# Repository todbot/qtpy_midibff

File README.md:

# qtpy_midibff

QTPy MIDI BFF — a small MIDI interface board for QTPy / Xiao class boards (RP2040 or compatible).
The board breaks out the host MCU's hardware UART to standard MIDI IN and MIDI OUT jacks (TRS or 5-pin DIN).

## Hardware

The PCB is meant for easy assembly using only through-hole components. 
It is essentialy a QTPy "doubler" with a standard MIDI In and MIDI Out circuit, 
with a 4-pin I2C header for a standard OLED display (usually 128x32 SSD1306).

## Assembling

_Coming soon._

## Arduino sketches

Requires [arduino-pico](https://arduino-pico.readthedocs.io/en/latest/install.html) board core.

Set **Tools > USB Stack: Adafruit TinyUSB** before uploading any sketch.

Libraries needed (Arduino Library Manager):
- [Adafruit TinyUSB](https://github.com/adafruit/Adafruit_TinyUSB_Arduino)
- [MIDI Library](https://github.com/FortySevenEffects/arduino_midi_library)
- [Adafruit SSD1306](https://github.com/adafruit/Adafruit_SSD1306) + [Adafruit GFX Library](https://github.com/adafruit/Adafruit-GFX-Library) _(OLED sketches only)_
- [Adafruit SPIFlash](https://github.com/adafruit/Adafruit_SPIFlash) + [SdFat - Adafruit Fork](https://github.com/adafruit/SdFat) + [ArduinoJson](https://arduinojson.org) _(MSC sketch only)_

### `midi_interface` — USB-MIDI ↔ UART-MIDI bridge

[`arduino/midi_interface/`](arduino/midi_interface/)

Forwards all MIDI between USB and UART in both directions. Includes scaffolding to filter or
transform messages — uncomment the examples or add your own:

- Drop realtime messages (clock, active sensing, etc.)
- Transpose notes on a channel
- Remap channels

```
arduino-cli compile \
  --fqbn rp2040:rp2040:adafruit_qtpy:usbstack=tinyusb \
  arduino/midi_interface
```

SysEx messages up to 127 bytes are forwarded. See the source for notes on larger SysEx.

### `midi_interface_oled` — bridge with OLED display

[`arduino/midi_interface_oled/`](arduino/midi_interface_oled/)

Same bridge as `midi_interface`, with a 128x32 SSD1306 I2C OLED that displays each incoming
message. Realtime messages (clock, active sensing) are forwarded but not shown, to avoid flicker.

```
arduino-cli compile \
  --fqbn rp2040:rp2040:adafruit_qtpy:usbstack=tinyusb \
  arduino/midi_interface_oled
```

### `midi_interface_msc` — bridge with USB flash drive and config file

[`arduino/midi_interface_msc/`](arduino/midi_interface_msc/)

Extends `midi_interface_oled` with a USB Mass Storage device backed by the RP2040's internal
flash (the filesystem partition). The drive contains a `config.json` file that controls runtime
behaviour — no recompile needed to change settings.

```json
{
  "name": "MIDI BFF",
  "manufacturer": "todbot",
  "filter_realtime": false,
  "transpose": 0
}
```

Edit `config.json` on the drive, eject it, then reset the board to apply the new settings.
The `filter_realtime` and `transpose` fields are applied in both directions.

Requires a board Flash Size setting that includes a 1MB filesystem partition. Compile commands for each supported board:

```
# QTPy RP2040 (8MB flash)
arduino-cli compile \
  --fqbn rp2040:rp2040:adafruit_qtpy:usbstack=tinyusb,flash=8388608_1048576 \
  arduino/midi_interface_msc

# Xiao RP2040 (2MB flash)
arduino-cli compile \
  --fqbn rp2040:rp2040:seeed_xiao_rp2040:usbstack=tinyusb,flash=2097152_1048576 \
  arduino/midi_interface_msc
```

### `midi_interface_simple` — simplified bridge for learners

[`arduino/midi_interface_simple/`](arduino/midi_interface_simple/)

Same USB-MIDI ↔ UART-MIDI bridge with the same filter/transform scaffolding, but with SysEx
handling and advanced notes removed. A good starting point if you just want to read and modify
the forwarding logic without the extra complexity.

```
arduino-cli compile \
  --fqbn rp2040:rp2040:adafruit_qtpy:usbstack=tinyusb \
  arduino/midi_interface_simple
```

## CircuitPython sketches

Requires CircuitPython 9+ firmware on the board.

Libraries needed:
- [tmidi](https://github.com/todbot/CircuitPython_TMIDI) — copy `tmidi.py` to `/lib/` on your device or install with `circup tmidi`
- [adafruit_ssd1306](https://github.com/adafruit/Adafruit_CircuitPython_SSD1306) — install with `circup install adafruit_ssd1306` _(OLED sketches only)_

### `midi_interface` — USB-MIDI ↔ UART-MIDI bridge

[`circuitpython/midi_interface/`](circuitpython/midi_interface/)

Forwards all MIDI between USB and UART in both directions. Same filter/transform scaffolding
as the Arduino version — uncomment the examples or add your own:

- Drop realtime messages (clock, active sensing, etc.)
- Transpose notes on a channel
- Remap channels

SysEx messages up to 127 bytes are forwarded. Increase the `sysex_buf_*` bytearray sizes in
the source to raise the limit.

Copy `code.py` to the root of your device, or copy the whole `midi_interface/` folder and
rename `code.py` to suit.

### `midi_interface_oled` — bridge with OLED display

[`circuitpython/midi_interface_oled/`](circuitpython/midi_interface_oled/)

Same bridge as `midi_interface`, with a 128x32 SSD1306 I2C OLED that displays each incoming
message. Realtime messages are forwarded but not shown, to avoid flicker. The sketch continues
as a plain MIDI bridge if no display is connected.

Copy `code.py` to the root of your device, or copy the whole `midi_interface_oled/` folder and
rename `code.py` to suit.

## Hardware

Schematic and PCB in `schematics/midi_bff/` (KiCad).

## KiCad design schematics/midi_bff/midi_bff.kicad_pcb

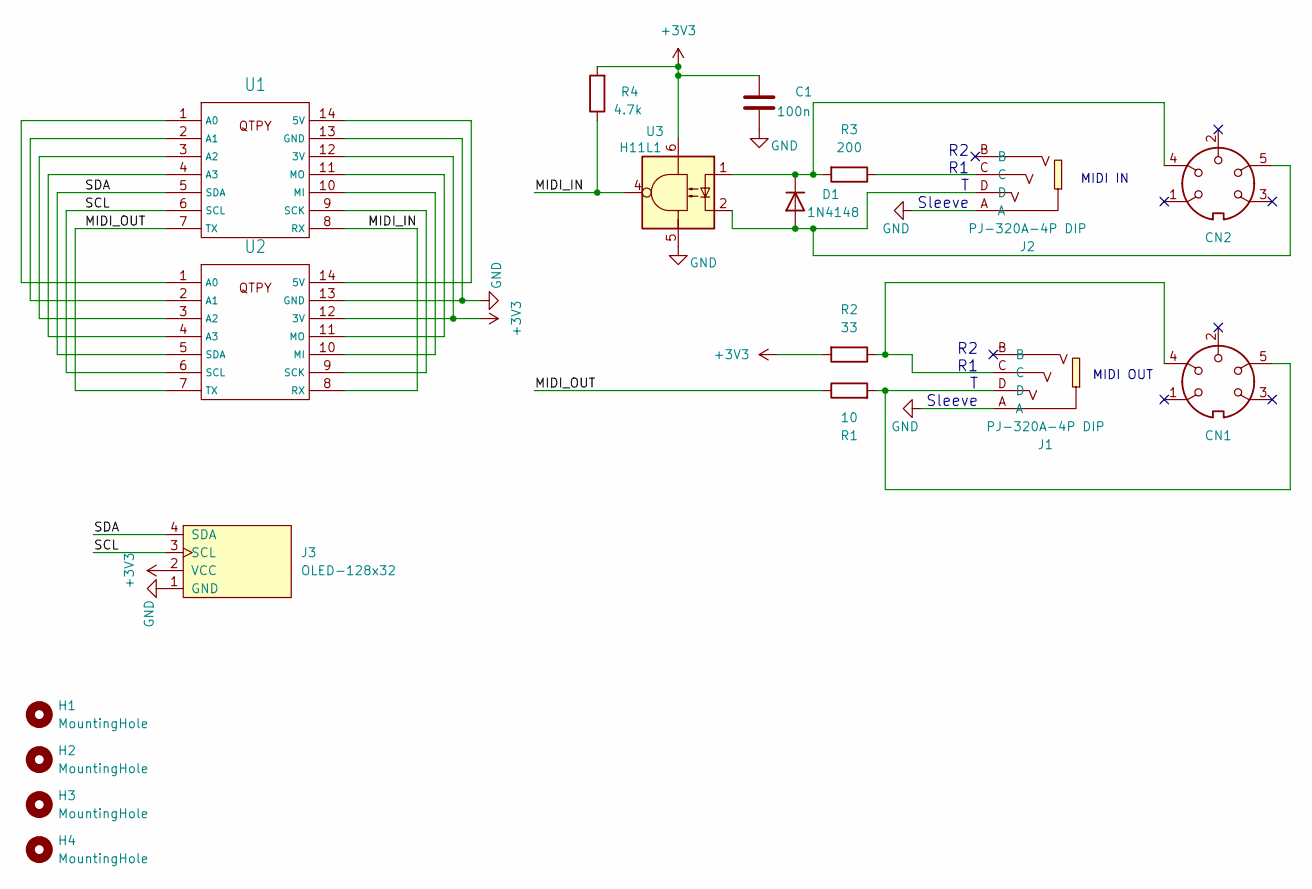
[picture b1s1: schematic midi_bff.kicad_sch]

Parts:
C1: 100n; C_Disc_D3.0mm_W1.6mm_P2.50mm; LCSC Part C1590
CN1, CN2: DIN-504; CONN-TH_DIN-504-M10; MPN DIN-504; LCSC Part C23689428
D1: 1N4148; D_DO-34_SOD68_P7.62mm_Horizontal; LCSC Part C81598
H1, H2, H3, H4: MountingHole; MountingHole_2.5mm
J1, J2: PJ-320A-4P DIP; AUDIO-TH_PJ-320A-4P-DIP; LCSC Part C18185602
J3: OLED-128x32
R1: 10; R_Axial_DIN0207_L6.3mm_D2.5mm_P7.62mm_Horizontal; LCSC Part C22859
R2: 33; R_Axial_DIN0207_L6.3mm_D2.5mm_P7.62mm_Horizontal; LCSC Part C23140
R3: 200; R_Axial_DIN0207_L6.3mm_D2.5mm_P7.62mm_Horizontal; LCSC Part C8218
R4: 4.7k; R_Axial_DIN0207_L6.3mm_D2.5mm_P7.62mm_Horizontal; LCSC Part C23162
U1, U2: QTPY-DIP
U3: H11L1; DIP-6_W7.62mm_Socket_LongPads; LCSC C78589

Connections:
+3V3: C1.1, J3.2 (VCC), R2.2, R4.2, U1.12 (3V), U2.12 (3V), U3.6
/MIDI_IN: R4.1, U1.8 (RX), U2.8 (RX), U3.4
/MIDI_OUT: R1.1, U1.7 (TX), U2.7 (TX)
/SCL: J3.3 (SCL), U1.6 (SCL), U2.6 (SCL)
/SDA: J3.4 (SDA), U1.5 (SDA), U2.5 (SDA)
GND: C1.2, J1.A, J2.A, J3.1 (GND), U1.13 (GND), U2.13 (GND), U3.5
unnamed: CN1.4, J1.C, R2.1
unnamed: CN1.5, J1.D, R1.2
unnamed: CN2.5, D1.2 (A), J2.D, U3.2
unnamed: CN2.4, D1.1 (K), R3.2, U3.1
unnamed: J2.C, R3.1
unnamed: U1.14 (5V), U2.14 (5V)
unnamed: U1.1 (A0), U2.1 (A0)
unnamed: U1.2 (A1), U2.2 (A1)
unnamed: U1.3 (A2), U2.3 (A2)
unnamed: U1.4 (A3), U2.4 (A3)
unnamed: U1.10 (MI), U2.10 (MI)
unnamed: U1.11 (MO), U2.11 (MO)
unnamed: U1.9 (SCK), U2.9 (SCK)

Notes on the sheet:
MIDI OUT
R2 R1 T Sleeve
MIDI IN

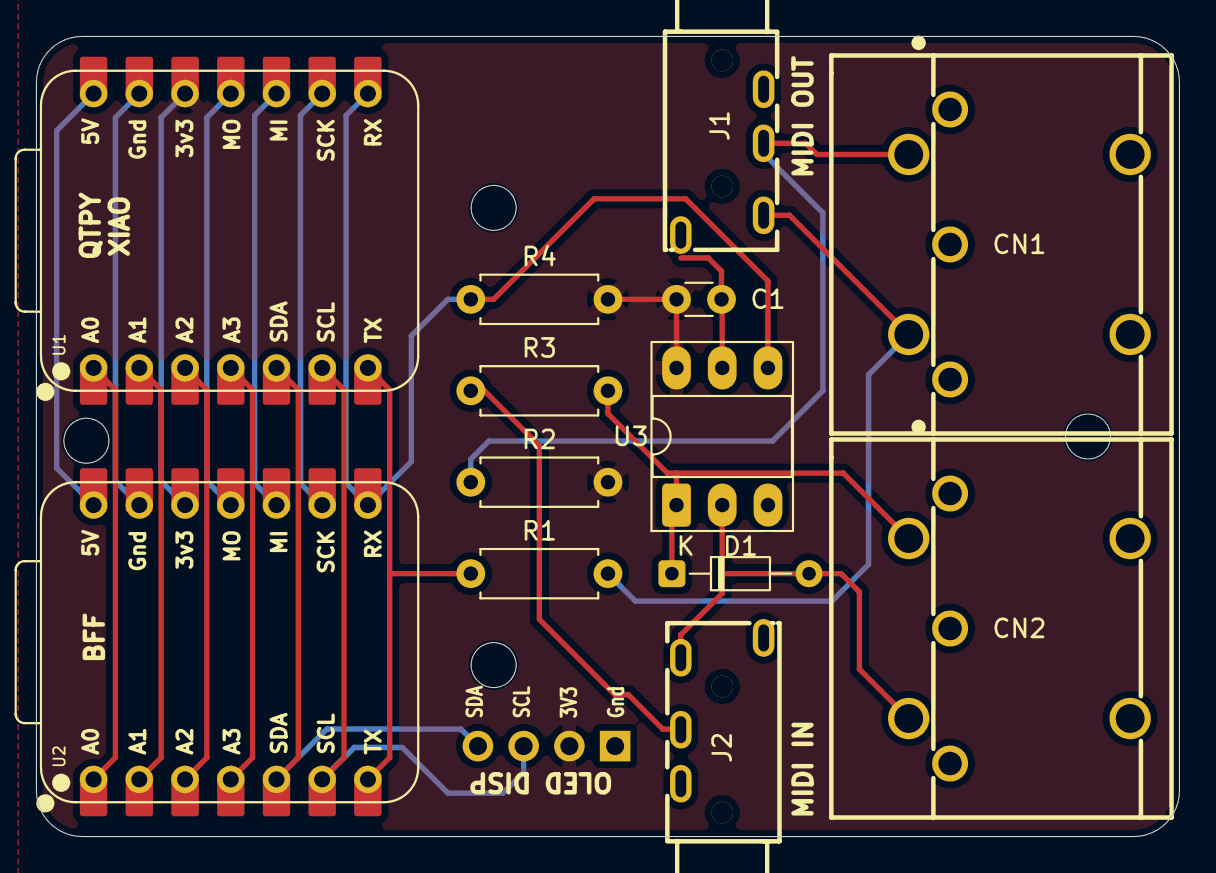
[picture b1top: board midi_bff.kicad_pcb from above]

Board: 2 copper layers, 63.5 x 44.4 mm, 18 parts (0 on the bottom side), 19 nets.

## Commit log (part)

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2022-07-31 sch brd
2022-08-01 added pic
2022-08-06 sigh trs-a/b will kill me
2026-05-10 new take on qtpy_midibff
2026-05-11 sent to production
2026-05-29 add first crack at arduino midi_interface
2026-05-29 new board img
2026-05-29 update gitignore
2026-05-29 update midi_interface to support sysex forwarding sorta, make midi_interface_simple that does not
2026-05-29 add circuitpython version of midi_interface
2026-05-30 add midi_interface_oled.ino
2026-05-30 add midi_interface_oled
2026-06-03 add midi_interface_msc. required making a custom FAT12 formatter
2026-06-11 resize to sch to A5
2026-06-12 add LED status to all Arduino sketches
